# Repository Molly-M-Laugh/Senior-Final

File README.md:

## Welcome to Our Senior Design Project!

### Hardware

Put some base organization, hardware files in general should be put into the overall hardware folder unless:

- Microcontroller, should go into a designated section of software rather (TBD)
- Finalized circuits, hardware spec docs, and fabric designs (and others TBD) have specific hardware sub-folders

### Software

This folder includes our work on everything in our software stack. We have our code for our ESP32 handling BLE communication, IOS app code, our frontend website, and our backend api.

### Citations
We use a third party library that has been included into our repository because it was the only way to upload our work to the phone that we are developing on without deploying it. The library is called Alamofire, it's used for HTTP communication in Swift. You can find it at Software/BLE-IOS/Alamofire

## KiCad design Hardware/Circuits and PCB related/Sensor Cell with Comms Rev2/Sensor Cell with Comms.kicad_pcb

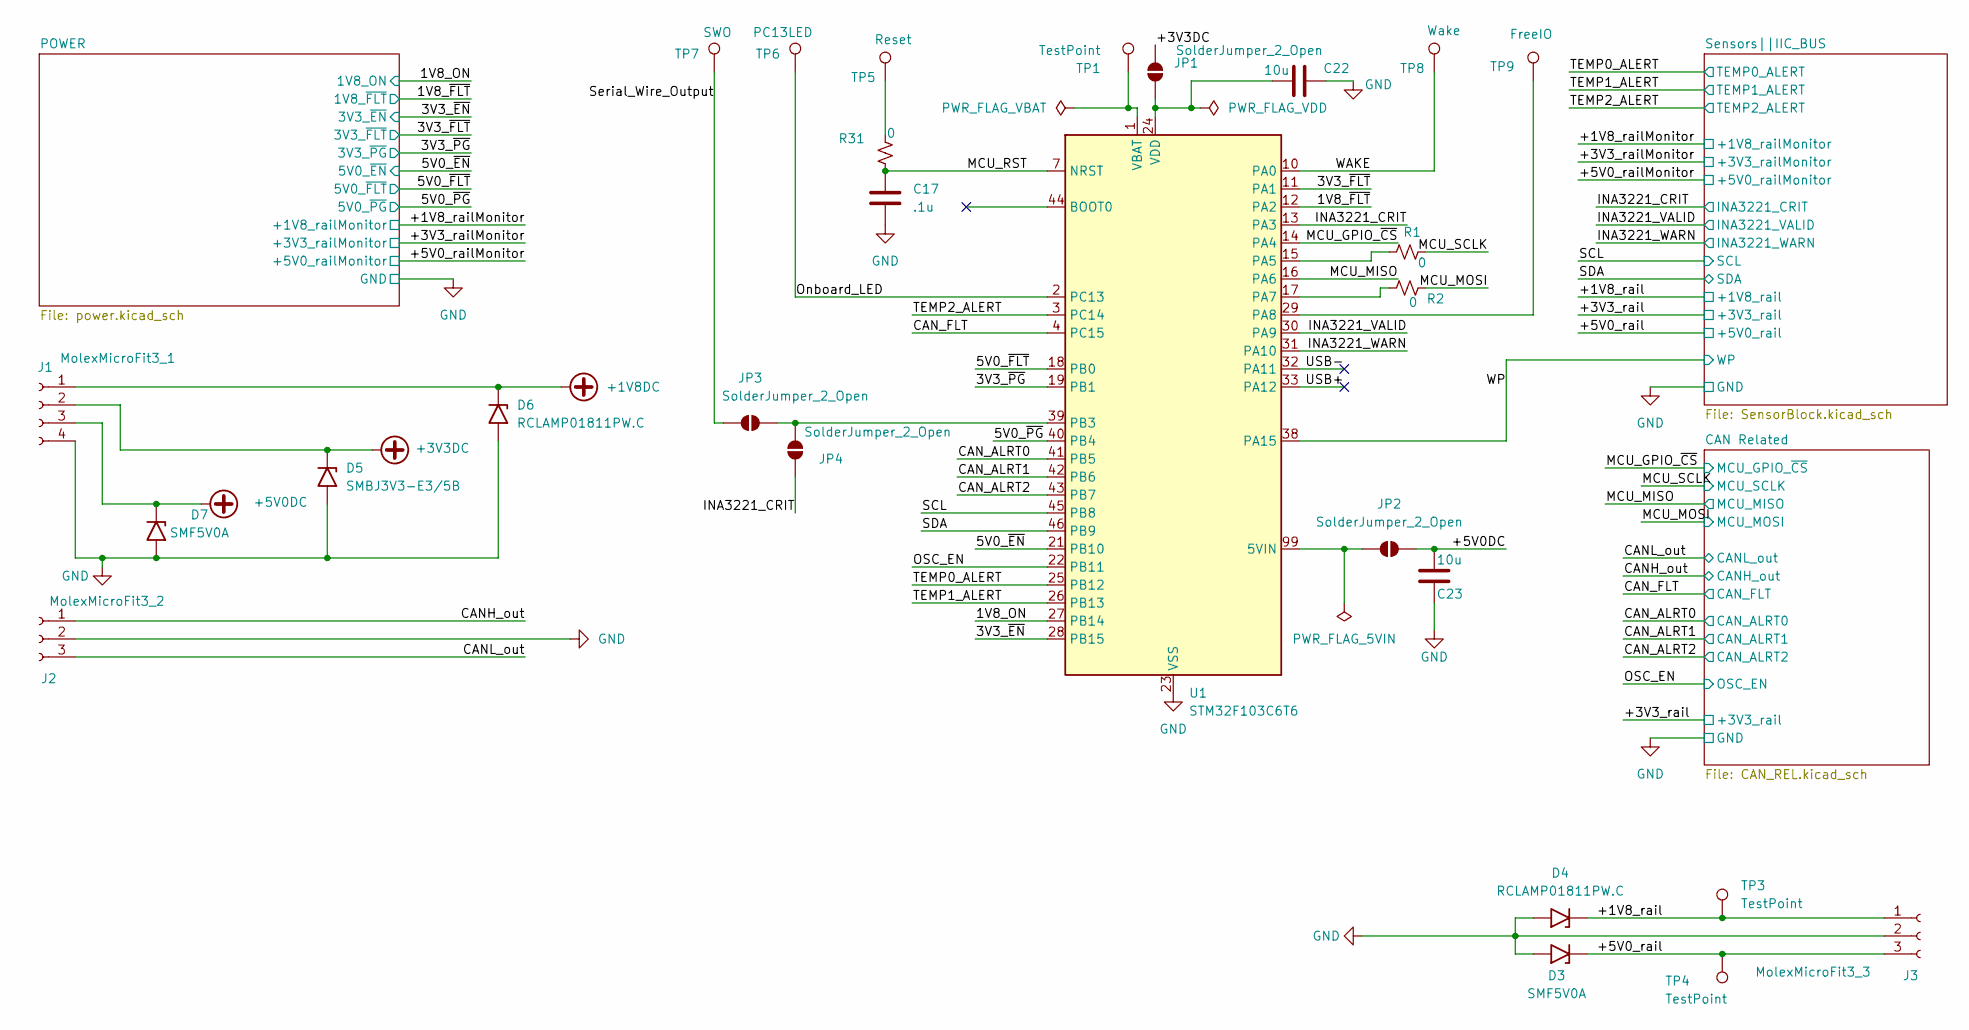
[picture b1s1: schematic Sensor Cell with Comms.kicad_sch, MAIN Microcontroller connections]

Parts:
C17: .1u; C_0805_2012Metric_Pad1.18x1.45mm_HandSolder
C22, C23: 10u; C_0603_1608Metric_Pad1.08x0.95mm_HandSolder
D3, D7: SMF5V0A; D_SMF
D4, D6: RCLAMP01811PW.C; D_SMF
D5: SMBJ3V3-E3/5B; D_SMF
J1: MolexMicroFit3_1; Molex_Micro-Fit_3.0_43650-0400_1x04_P3.00mm_Horizontal
J2: MolexMicroFit3_2; CONN_SD-43650-001_03_MOL
J3: MolexMicroFit3_3; CONN_SD-43650-001_03_MOL
JP1, JP2, JP3, JP4: SolderJumper_2_Open; SolderJumper-2_P1.3mm_Open_TrianglePad1.0x1.5mm
R1, R2, R31: 0; R_0603_1608Metric_Pad0.98x0.95mm_HandSolder
TP1, TP3, TP4: TestPoint; PinHeader_1x01_P1.00mm_Vertical
TP5: Reset; PinHeader_1x01_P1.00mm_Vertical
TP6: PC13LED; PinHeader_1x01_P1.00mm_Vertical
TP7: SWO; PinHeader_1x01_P1.00mm_Vertical
TP8: Wake; PinHeader_1x01_P1.00mm_Vertical
TP9: FreeIO; PinHeader_1x01_P1.00mm_Vertical
U1: STM32F103C6T6; PinHeader_1x20_P1.00mm_Verticalx2

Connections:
+1V8DC: D6.1 (A1), J1.1; also elsewhere on the board
+3V3DC: D5.1 (A1), J1.2, JP1.2 (B); also elsewhere on the board
+5V0DC: C23.2, D7.1 (A1), J1.3, JP2.2 (B); also elsewhere on the board
/1V8_ON: U1.27 (PB14); also elsewhere on the board
/1V8_~FLT: U1.12 (PA2); also elsewhere on the board
/3V3_~EN: U1.28 (PB15); also elsewhere on the board
/3V3_~FLT: U1.11 (PA1); also elsewhere on the board
/3V3_~PG: U1.19 (PB1); also elsewhere on the board
/5V0_~EN: U1.21 (PB10); also elsewhere on the board
/5V0_~FLT: U1.18 (PB0); also elsewhere on the board
/5V0_~PG: U1.40 (PB4); also elsewhere on the board
/+1V8_rail: D4.1 (A1), J3.1, TP3.1; also elsewhere on the board
/+5V0_rail: D3.1 (A1), J3.3, TP4.1; also elsewhere on the board
/CANH_out: J2.1; also elsewhere on the board
/CANL_out: J2.3; also elsewhere on the board
/CAN_ALRT0: U1.41 (PB5); also elsewhere on the board
/CAN_ALRT1: U1.42 (PB6); also elsewhere on the board
/CAN_ALRT2: U1.43 (PB7); also elsewhere on the board
/CAN_FLT: U1.4 (PC15); also elsewhere on the board
/INA3221_CRIT: JP4.2 (B), U1.13 (PA3); also elsewhere on the board
/INA3221_VALID: U1.30 (PA9); also elsewhere on the board
/INA3221_WARN: U1.31 (PA10); also elsewhere on the board
/MCU_GPIO_~CS: U1.14 (PA4); also elsewhere on the board
/MCU_MISO: U1.16 (PA6); also elsewhere on the board
/MCU_MOSI: R2.1; also elsewhere on the board
/MCU_RST: C17.1, R31.2, U1.7 (NRST)
/MCU_SCLK: R1.1; also elsewhere on the board
/OSC_EN: U1.22 (PB11); also elsewhere on the board
/Onboard_LED: TP6.1, U1.2 (PC13)
/SCL: U1.45 (PB8); also elsewhere on the board
/SDA: U1.46 (PB9); also elsewhere on the board
/Serial_Wire_Output: JP3.1 (A), TP7.1
/TEMP0_ALERT: U1.25 (PB12); also elsewhere on the board
/TEMP1_ALERT: U1.26 (PB13); also elsewhere on the board
/TEMP2_ALERT: U1.3 (PC14); also elsewhere on the board
/USB+: U1.33 (PA12)
/USB-: U1.32 (PA11)
/WAKE: TP8.1, U1.10 (PA0)
/WP: U1.38 (PA15); also elsewhere on the board
unnamed: JP2.1 (A), U1.99 (5VIN)
unnamed: JP3.2 (B), JP4.1 (A), U1.39 (PB3)
unnamed: R31.1, TP5.1
unnamed: R1.2, U1.15 (PA5)
unnamed: R2.2, U1.17 (PA7)
unnamed: TP9.1, U1.29 (PA8)
unnamed: TP1.1, U1.1 (VBAT)

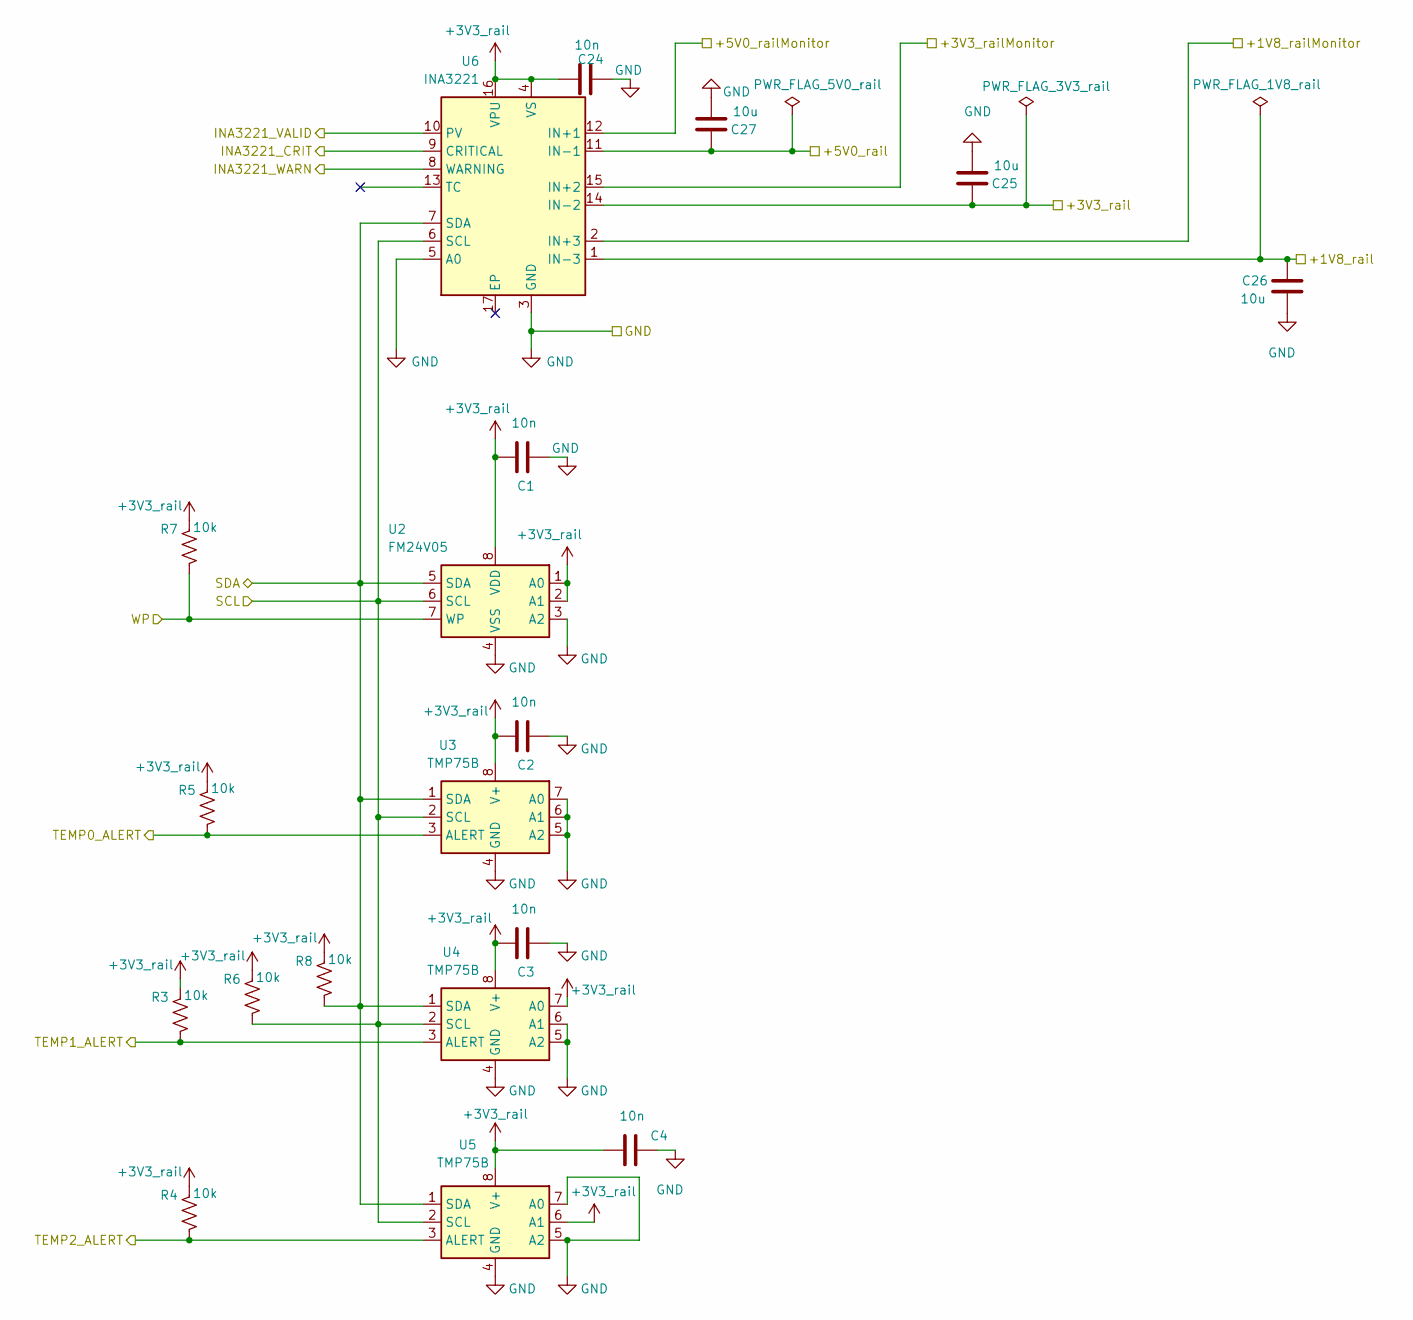
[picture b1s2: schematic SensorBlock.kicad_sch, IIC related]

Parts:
C1, C2, C3, C4, C24: 10n; C_0603_1608Metric_Pad1.08x0.95mm_HandSolder
C25, C26, C27: 10u; C_0603_1608Metric_Pad1.08x0.95mm_HandSolder
R3, R4, R5, R6, R7, R8: 10k; R_0603_1608Metric_Pad0.98x0.95mm_HandSolder
U2: FM24V05; SOIC-8_3.9x4.9mm_P1.27mm
U3, U4, U5: TMP75B; SO-8_3.9x4.9mm_P1.27mm
U6: INA3221; PinHeader_1x08_P1.00mm_Vertical_addedMonitorLines

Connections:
+3V3_rail: C1.2, C2.2, C3.2, C4.2, C24.2, C25.2, R3.2, R4.2, R5.2, R6.2, R7.2, R8.2, U2.1 (A0), U2.2 (A1), U2.8 (VDD), U3.8 (V+), U4.7 (A0), U4.8 (V+), U5.6 (A1), U5.8 (V+), U6.4 (VS), U6.14 (IN-2), U6.16 (VPU); also elsewhere on the board
/+1V8_rail: C26.2, U6.1 (IN-3); also elsewhere on the board
/+1V8_railMonitor: U6.2 (IN+3); also elsewhere on the board
/+3V3_railMonitor: U6.15 (IN+2); also elsewhere on the board
/+5V0_rail: C27.2, U6.11 (IN-1); also elsewhere on the board
/+5V0_railMonitor: U6.12 (IN+1); also elsewhere on the board
/INA3221_CRIT: U6.9 (CRITICAL); also elsewhere on the board
/INA3221_VALID: U6.10 (PV); also elsewhere on the board
/INA3221_WARN: U6.8 (WARNING); also elsewhere on the board
/SCL: R6.1, U2.6 (SCL), U3.2 (SCL), U4.2 (SCL), U5.2 (SCL), U6.6 (SCL); also elsewhere on the board
/SDA: R8.1, U2.5 (SDA), U3.1 (SDA), U4.1 (SDA), U5.1 (SDA), U6.7 (SDA); also elsewhere on the board
/TEMP0_ALERT: R5.1, U3.3 (ALERT); also elsewhere on the board
/TEMP1_ALERT: R3.1, U4.3 (ALERT); also elsewhere on the board
/TEMP2_ALERT: R4.1, U5.3 (ALERT); also elsewhere on the board
/WP: R7.1, U2.7 (WP); also elsewhere on the board

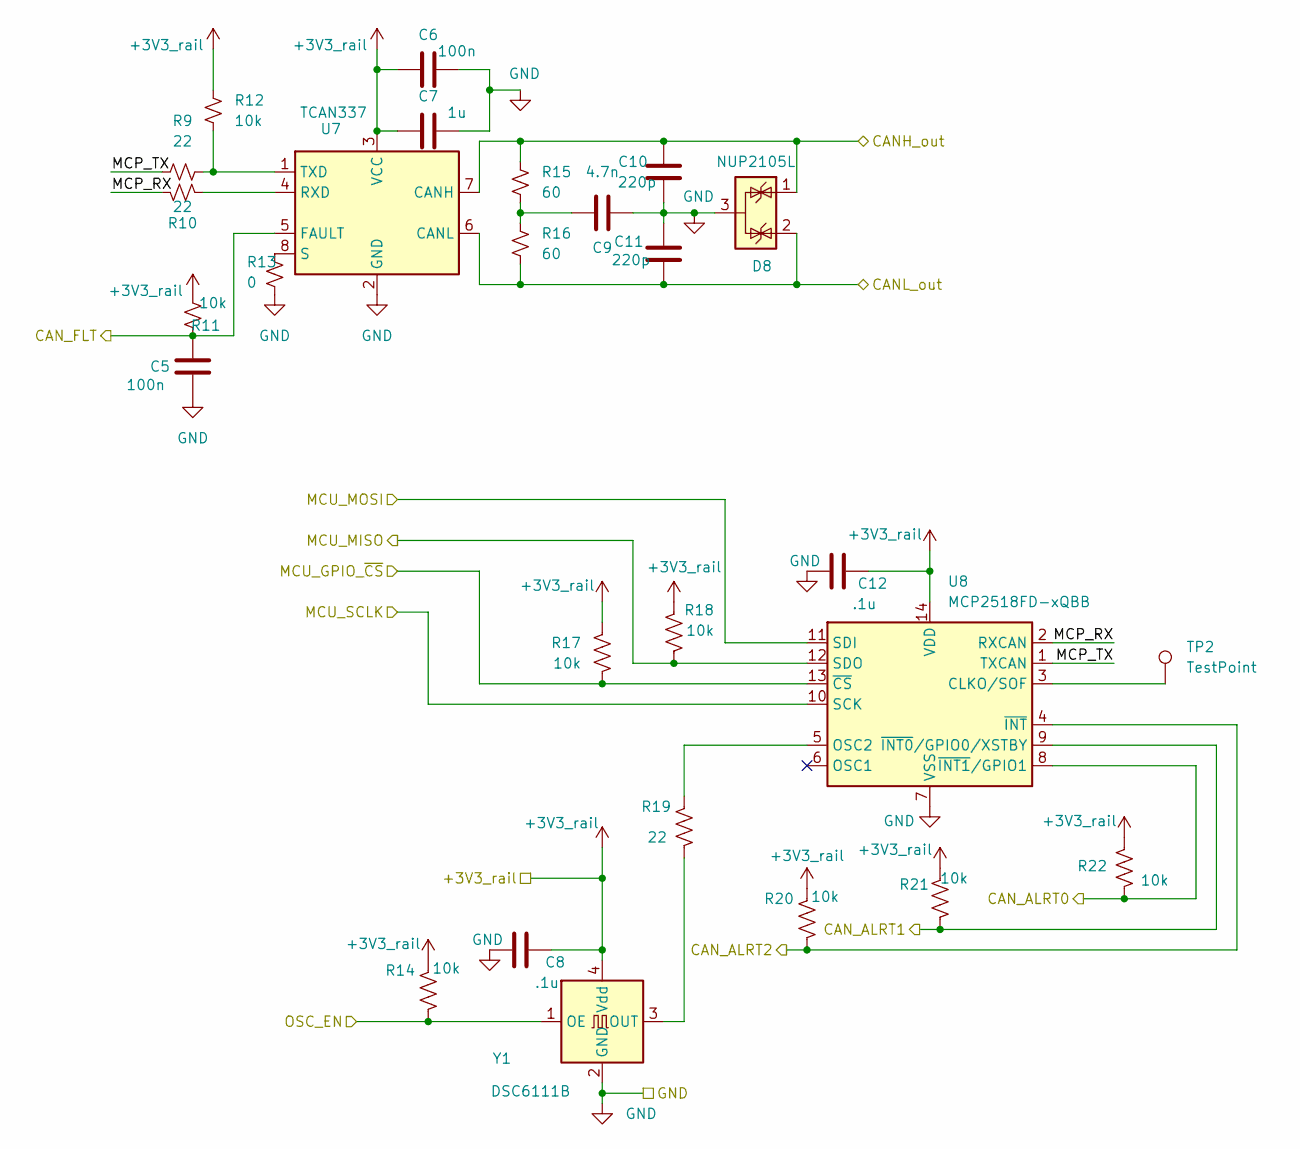
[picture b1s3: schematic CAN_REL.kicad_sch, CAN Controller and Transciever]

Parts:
C5, C6: 100n; C_0603_1608Metric_Pad1.08x0.95mm_HandSolder
C7: 1u; C_0603_1608Metric_Pad1.08x0.95mm_HandSolder
C8, C12: .1u; C_0603_1608Metric_Pad1.08x0.95mm_HandSolder
C9: 4.7n; C_0603_1608Metric_Pad1.08x0.95mm_HandSolder
C10, C11: 220p; C_0603_1608Metric_Pad1.08x0.95mm_HandSolder
D8: NUP2105L; SOT-23
R9, R10, R19: 22; R_0603_1608Metric_Pad0.98x0.95mm_HandSolder
R11, R12, R14, R17, R18, R20, R21, R22: 10k; R_0603_1608Metric_Pad0.98x0.95mm_HandSolder
R13: 0; R_0603_1608Metric_Pad0.98x0.95mm_HandSolder
R15, R16: 60; R_0603_1608Metric_Pad0.98x0.95mm_HandSolder
TP2: TestPoint; PinHeader_1x01_P1.00mm_Vertical
U7: TCAN337; SOIC-8_3.9x4.9mm_P1.27mm
U8: MCP2518FD-xQBB; SOIC-14_3.9x8.7mm_P1.27mm
Y1: DSC6111B; Oscillator_SMD_SiT_PQFN-4Pin_2.0x1.6mm

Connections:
+3V3_rail: C6.2, C7.2, C8.2, C12.2, R11.1, R12.2, R14.2, R17.2, R18.2, R20.2, R21.2, R22.2, U7.3 (VCC), U8.14 (VDD), Y1.4 (Vdd); also elsewhere on the board
/CAN Related/MCP_RX: R10.1, U8.2 (RXCAN)
/CAN Related/MCP_TX: R9.2, U8.1 (TXCAN)
/CANH_out: C10.2, D8.1 (K), R15.1, U7.7 (CANH); also elsewhere on the board
/CANL_out: C11.1, D8.2 (K), R16.2, U7.6 (CANL); also elsewhere on the board
/CAN_ALRT0: R22.1, U8.8 (~INT1/GPIO1); also elsewhere on the board
/CAN_ALRT1: R21.1, U8.9 (~INT0/GPIO0/XSTBY); also elsewhere on the board
/CAN_ALRT2: R20.1, U8.4 (~INT); also elsewhere on the board
/CAN_FLT: C5.2, R11.2, U7.5 (FAULT); also elsewhere on the board
/MCU_GPIO_~CS: R17.1, U8.13 (~CS); also elsewhere on the board
/MCU_MISO: R18.1, U8.12 (SDO); also elsewhere on the board
/MCU_MOSI: U8.11 (SDI); also elsewhere on the board
/MCU_SCLK: U8.10 (SCK); also elsewhere on the board
/OSC_EN: R14.1, Y1.1 (OE); also elsewhere on the board
unnamed: C9.1, R15.2, R16.1
unnamed: R10.2, U7.4 (RXD)
unnamed: R13.2, U7.8 (S)
unnamed: R9.1, R12.1, U7.1 (TXD)
unnamed: TP2.1, U8.3 (CLKO/SOF)
unnamed: R19.2, U8.5 (OSC2)
unnamed: R19.1, Y1.3 (OUT)

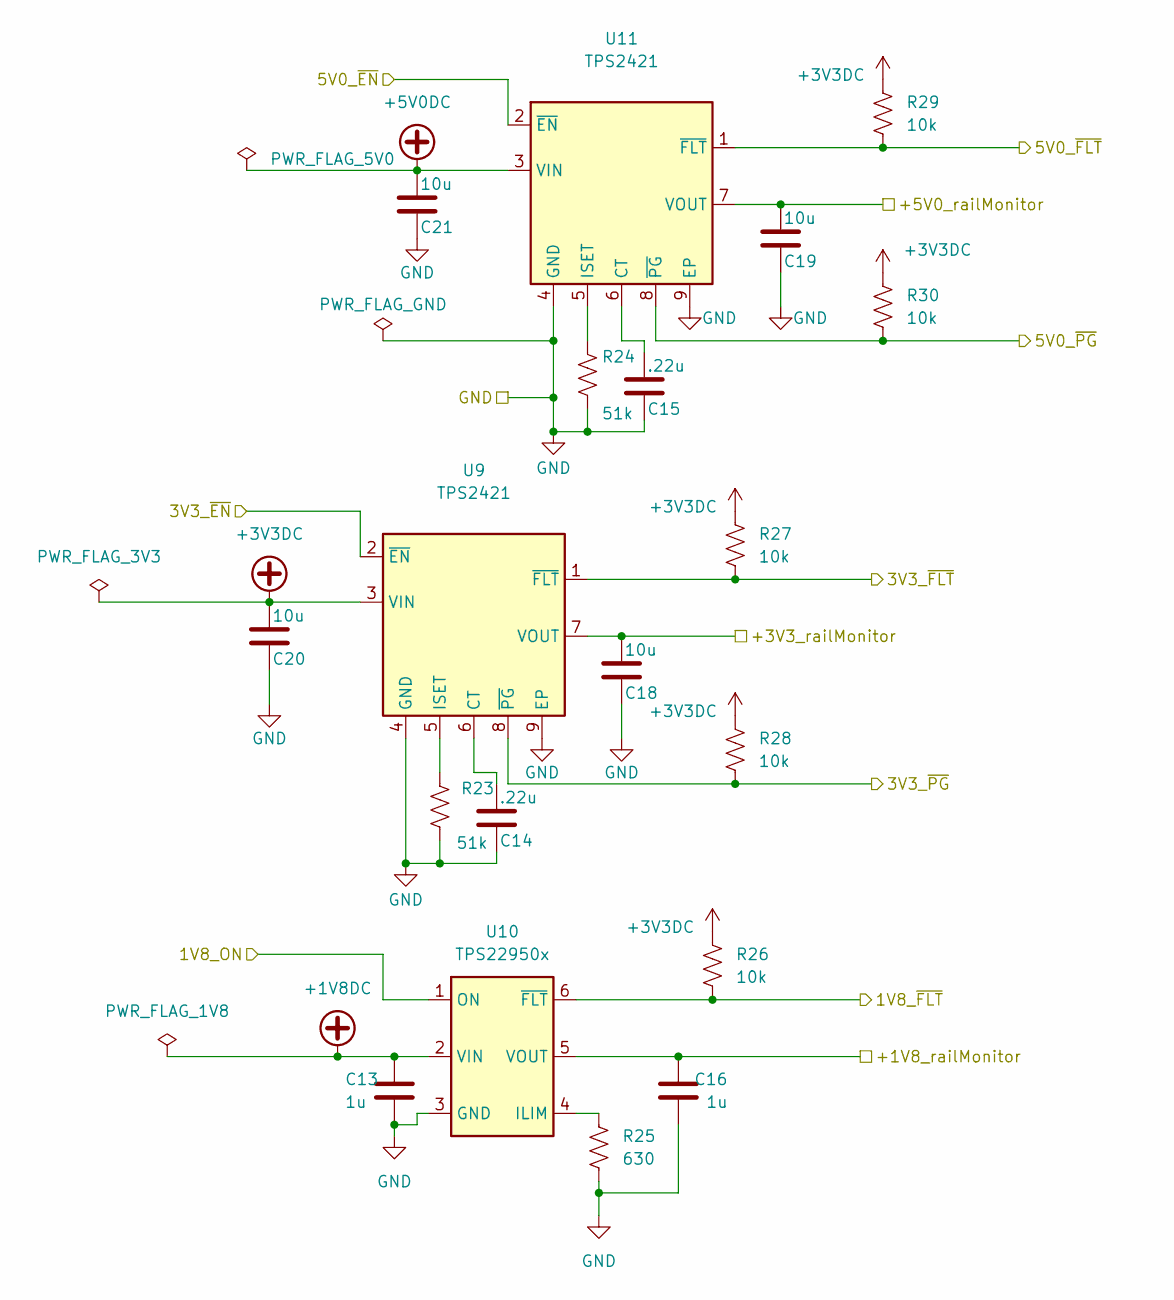
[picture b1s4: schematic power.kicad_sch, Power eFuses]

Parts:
C13, C16: 1u; C_0603_1608Metric_Pad1.08x0.95mm_HandSolder
C14, C15: .22u; C_0603_1608Metric_Pad1.08x0.95mm_HandSolder
C18, C19, C20, C21: 10u; C_0603_1608Metric_Pad1.08x0.95mm_HandSolder
R23, R24: 51k; R_0603_1608Metric_Pad0.98x0.95mm_HandSolder
R25: 630; R_0603_1608Metric_Pad0.98x0.95mm_HandSolder
R26, R27, R28, R29, R30: 10k; R_0603_1608Metric_Pad0.98x0.95mm_HandSolder
U9, U11: TPS2421; HSOP-8-1EP_3.9x4.9mm_P1.27mm_EP2.41x3.1mm_ThermalVias
U10: TPS22950x; SOT-23-6

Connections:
+1V8DC: C13.2, U10.2 (VIN); also elsewhere on the board
+3V3DC: C20.2, R26.2, R27.2, R28.2, R29.2, R30.2, U9.3 (VIN); also elsewhere on the board
+5V0DC: C21.2, U11.3 (VIN); also elsewhere on the board
/1V8_ON: U10.1 (ON); also elsewhere on the board
/1V8_~FLT: R26.1, U10.6 (~FLT); also elsewhere on the board
/3V3_~EN: U9.2 (~EN); also elsewhere on the board
/3V3_~FLT: R27.1, U9.1 (~FLT); also elsewhere on the board
/3V3_~PG: R28.1, U9.8 (~PG); also elsewhere on the board
/5V0_~EN: U11.2 (~EN); also elsewhere on the board
/5V0_~FLT: R29.1, U11.1 (~FLT); also elsewhere on the board
/5V0_~PG: R30.1, U11.8 (~PG); also elsewhere on the board
/+1V8_railMonitor: C16.2, U10.5 (VOUT); also elsewhere on the board
/+3V3_railMonitor: C18.2, U9.7 (VOUT); also elsewhere on the board
/+5V0_railMonitor: C19.2, U11.7 (VOUT); also elsewhere on the board
unnamed: C14.2, U9.6 (CT)
unnamed: R23.2, U9.5 (ISET)
unnamed: R25.2, U10.4 (ILIM)
unnamed: C15.2, U11.6 (CT)
unnamed: R24.2, U11.5 (ISET)

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
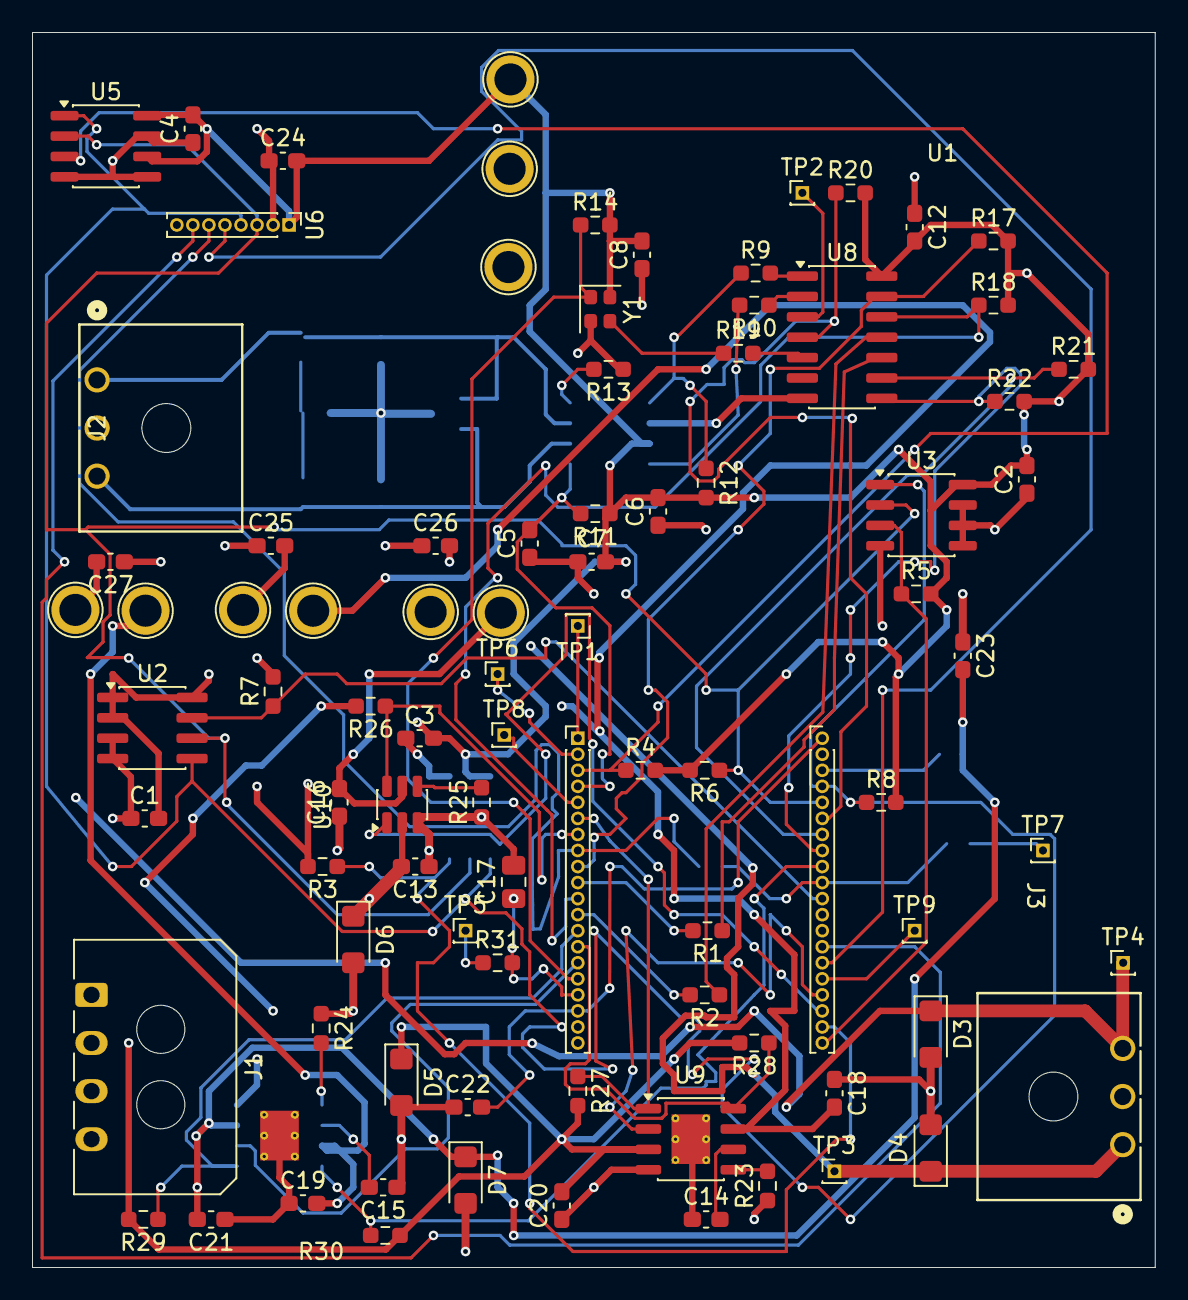
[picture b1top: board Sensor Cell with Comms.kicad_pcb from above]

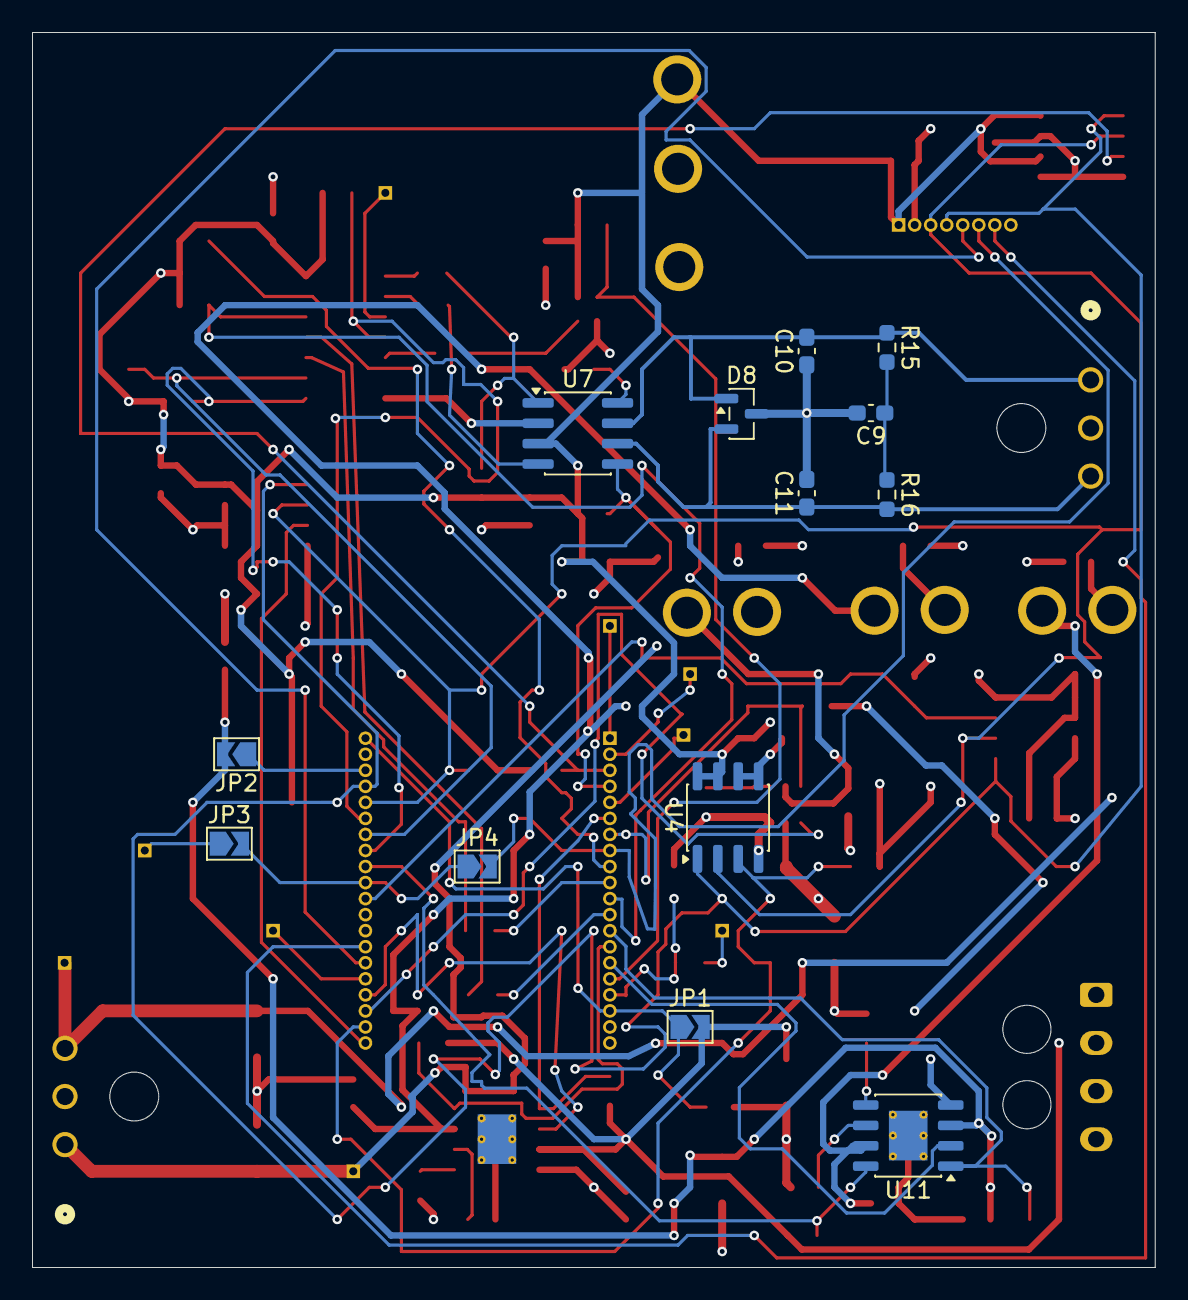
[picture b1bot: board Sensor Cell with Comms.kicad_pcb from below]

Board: 4 copper layers, 70.0 x 77.0 mm, 92 parts (13 on the bottom side), 64 nets.

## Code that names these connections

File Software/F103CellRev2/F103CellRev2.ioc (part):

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Mcu.Name=STM32F103C(4-6)Tx
Mcu.Package=LQFP48
Mcu.UserName=STM32F103C6Tx
PA0-WKUP.GPIOParameters=GPIO_Label
PA0-WKUP.GPIO_Label=WAKE
PA0-WKUP.Mode=SYS_WakeUp0
PA0-WKUP.Signal=SYS_WKUP
PA1.GPIOParameters=GPIO_Label,GPIO_ModeDefaultEXTI
PA1.GPIO_Label=FLT_3V3
PA1.GPIO_ModeDefaultEXTI=GPIO_MODE_IT_FALLING
PA1.Signal=GPXTI1
PA10.GPIOParameters=GPIO_Label,GPIO_ModeDefaultEXTI
PA10.GPIO_Label=INA3221_WARN
PA10.GPIO_ModeDefaultEXTI=GPIO_MODE_IT_FALLING
PA10.Signal=GPXTI10
PA11.GPIOParameters=GPIO_Label
PA11.GPIO_Label=USB-
PA11.Mode=Device
PA11.Signal=USB_DM
PA12.GPIOParameters=GPIO_Label
PA12.GPIO_Label=USB+
PA12.Mode=Device
PA12.Signal=USB_DP
PA13.Mode=Serial_Wire
PA13.Signal=SYS_JTMS-SWDIO
PA14.Mode=Serial_Wire
PA14.Signal=SYS_JTCK-SWCLK
PA15.GPIOParameters=PinState,GPIO_Label
PA15.GPIO_Label=WP
PA15.PinState=GPIO_PIN_SET
PA15.Signal=GPIO_Output
PA2.GPIOParameters=GPIO_Label,GPIO_ModeDefaultEXTI
PA2.GPIO_Label=FLT_1V8
PA2.GPIO_ModeDefaultEXTI=GPIO_MODE_IT_FALLING
PA2.Signal=GPXTI2
PA3.GPIOParameters=GPIO_Label,GPIO_ModeDefaultEXTI
PA3.GPIO_Label=INA3221_CRIT
PA3.GPIO_ModeDefaultEXTI=GPIO_MODE_IT_FALLING
PA3.Signal=GPXTI3
PA4.GPIOParameters=PinState,GPIO_Label
PA4.GPIO_Label=SPI_CS
PA4.PinState=GPIO_PIN_SET
PA4.Signal=GPIO_Output
PA5.GPIOParameters=GPIO_Label
PA5.GPIO_Label=MCU_SCLK
PA5.Mode=Full_Duplex_Master
PA5.Signal=SPI1_SCK
PA6.GPIOParameters=GPIO_Label
PA6.GPIO_Label=MCU_MISO
PA6.Mode=Full_Duplex_Master
PA6.Signal=SPI1_MISO
PA7.GPIOParameters=GPIO_Label
PA7.GPIO_Label=MCU_MOSI
PA7.Mode=Full_Duplex_Master
PA7.Signal=SPI1_MOSI
PA8.GPIOParameters=GPIO_Label
PA8.GPIO_Label=FreeIO
PA8.Signal=GPIO_Output
PA9.GPIOParameters=GPIO_Label,GPIO_ModeDefaultEXTI
PA9.GPIO_Label=INA3221_VALID
PA9.GPIO_ModeDefaultEXTI=GPIO_MODE_IT_FALLING
PA9.Signal=GPXTI9
PB0.GPIOParameters=GPIO_Label,GPIO_ModeDefaultEXTI
PB0.GPIO_Label=FLT_5V0
PB0.GPIO_ModeDefaultEXTI=GPIO_MODE_IT_FALLING
PB0.Signal=GPXTI0
PB1.GPIOParameters=GPIO_Label
PB1.GPIO_Label=PG3V3
PB1.Signal=GPIO_Input
PB10.GPIOParameters=PinState,GPIO_Label
PB10.GPIO_Label=EN5V0
PB10.PinState=GPIO_PIN_SET
PB10.Signal=GPIO_Output
PB11.GPIOParameters=GPIO_Label
PB11.GPIO_Label=OSC_EN
PB11.Signal=GPIO_Output
PB12.GPIOParameters=GPIO_Label,GPIO_ModeDefaultEXTI
PB12.GPIO_Label=TEMP0_ALERT
PB12.GPIO_ModeDefaultEXTI=GPIO_MODE_IT_FALLING
PB12.Signal=GPXTI12
PB13.GPIOParameters=GPIO_Label,GPIO_ModeDefaultEXTI
PB13.GPIO_Label=TEMP1_ALERT
PB13.GPIO_ModeDefaultEXTI=GPIO_MODE_IT_FALLING
PB13.Signal=GPXTI13
PB14.GPIOParameters=GPIO_Label
PB14.GPIO_Label=ON1V8
PB14.Signal=GPIO_Output
PB15.GPIOParameters=PinState,GPIO_Label
PB15.GPIO_Label=EN3V3
PB15.PinState=GPIO_PIN_SET
PB15.Signal=GPIO_Output
PB3.GPIOParameters=GPIO_Label
PB3.GPIO_Label=SingleWireOutput
PB3.Signal=SYS_JTDO-TRACESWO
PB4.GPIOParameters=GPIO_Label,GPIO_ModeDefaultEXTI
PB4.GPIO_Label=PG5V0
PB4.GPIO_ModeDefaultEXTI=GPIO_MODE_IT_FALLING
PB4.Signal=GPXTI4
PB5.GPIOParameters=GPIO_Label,GPIO_ModeDefaultEXTI
PB5.GPIO_Label=CAN_ALRT0
PB5.GPIO_ModeDefaultEXTI=GPIO_MODE_IT_FALLING
PB5.Signal=GPXTI5
PB6.GPIOParameters=GPIO_Label,GPIO_ModeDefaultEXTI
PB6.GPIO_Label=CAN_ALRT1
PB6.GPIO_ModeDefaultEXTI=GPIO_MODE_IT_FALLING
PB6.Signal=GPXTI6
PB7.GPIOParameters=GPIO_Label,GPIO_ModeDefaultEXTI
PB7.GPIO_Label=CAN_ALRT2
PB7.GPIO_ModeDefaultEXTI=GPIO_MODE_IT_FALLING
PB7.Signal=GPXTI7
PB8.GPIOParameters=GPIO_Label
PB8.GPIO_Label=SCL
PB8.Mode=I2C
PB8.Signal=I2C1_SCL
PB9.GPIOParameters=GPIO_Label
PB9.GPIO_Label=SDA
PB9.Mode=I2C
PB9.Signal=I2C1_SDA
PC13-TAMPER-RTC.GPIOParameters=GPIO_Label
PC13-TAMPER-RTC.GPIO_Label=OnboardLED
PC13-TAMPER-RTC.Signal=GPIO_Output
PC14-OSC32_IN.GPIOParameters=GPIO_Label,GPIO_ModeDefaultEXTI
PC14-OSC32_IN.GPIO_Label=TEMP2_ALERT
PC14-OSC32_IN.GPIO_ModeDefaultEXTI=GPIO_MODE_IT_FALLING
PC14-OSC32_IN.Signal=GPXTI14
PC15-OSC32_OUT.GPIOParameters=GPIO_Label,GPIO_ModeDefaultEXTI
PC15-OSC32_OUT.GPIO_Label=CAN_FLT
PC15-OSC32_OUT.GPIO_ModeDefaultEXTI=GPIO_MODE_IT_FALLING
PC15-OSC32_OUT.Signal=GPXTI15
PD0-OSC_IN.Mode=HSE-External-Oscillator
PD0-OSC_IN.Signal=RCC_OSC_IN
PD1-OSC_OUT.Mode=HSE-External-Oscillator
PD1-OSC_OUT.Signal=RCC_OSC_OUT
RCC.SYSCLKFreq_VALUE=72000000
RCC.SYSCLKSource=RCC_SYSCLKSOURCE_PLLCLK
board=custom

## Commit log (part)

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2026-01-02 Adding base design folders
    Please remove the keep.txt once files are added to that folder, is just so GitHub would see the file for upload.
2026-01-02 Create README.md
    Describing current drafted layout
2026-01-02 Added safety docs
    IEC documents on safety, hazards, batteries, etc
2026-01-10 Removed the added RouterLink while is only one page
2026-01-10 Readded RouterLink as routing still not retrieved, added zone.js for local routing
2026-01-10 Forgot to ng build, now seeing if changes cascade to heroku
2026-01-10 Trying some build path changes
2026-01-10 Continuing to find alternative routing for newer node version
2026-01-10 Rolling back package.json and server.js changes
2026-01-10 Forgot to rename server paths from lab3
2026-01-11 Forgot ng build, redoing to see Heroku changes
2026-01-11 Added zone.js to component's .ts files to see effect
2026-01-11 Attempting to find heroku routing again
2026-01-11 Cloned lab 3 on last working heroku branch, now working on confirming heroku acceptance
2026-01-11 Forgot to resolve one merge conflicted file
2026-01-11 Removed and/or renamed components and references to reflect senior project's pages
2026-01-18 Added fabric docs
2026-01-19 Testing login without form live updates/routing with auth included
2026-01-19 Added empty function to check login display currently
2026-01-19 Forgot name of form group
2026-01-19 Now can see password input box, added but not linking auth/mailer under services folder
2026-01-29 Switched to earlier version to work on pure routing before try authentication
2026-02-01 Added sewing/surger documentation
    For future work or report reference
2026-02-02 Confirmed high chance is an ssr issue for any auto routes to an ngform, will work on ssr now
2026-02-03 Added SSR so that base page can point to a form without invalidating the form
2026-02-03 Forgot npm install, and changed output directory to reflect newer angular ssr
2026-02-07 Adding last of base pages for routing before additional authentication, sql access
2026-02-07 Adding BLE communication work from past month
2026-02-10 Rename Cell Supervisor.pdf to Cell Supervisor. rev1pdf
2026-02-10 Rename Cell Supervisor. rev1pdf to Cell Supervisor_rev1.pdf
2026-02-14 Added some base components for local sql server connection, but need to set up HTTPClient
2026-02-14 Added HTTPClient, now debugging connection to local server
2026-02-14 Added components for initial connection from nodejs to postgres, but have to fix issue with angular/nodejs firewall
2026-02-17 Added comments, removed code for testing BLE functionality.
2026-02-17 Made progress in trying to implement the browser side rendering graph library, but will shift real quick to finding/using an SSR safe graph library
2026-02-18 Added Heroku allowed origins
2026-02-18 Heroku having a general issue saying cors not defined, so with no SQL currently dropping cors origin verification for now
2026-02-21 Create info.txt
    info about items in this folder and subfolders
2026-02-22 Making work on getting cors working, as is inter-server connection issue based on Dev Tools
2026-02-22 Wanted to complete local SQL and knew where base issues were, so got feedback on CORS/API location, URL slight syntax and visability, and additional routing/button hold on registration
2026-02-22 Changing heroku postbuild to see both angular and nodejs?
2026-02-22 Changing heroku postbuild to see both angular and nodejs v2?
2026-02-22 Changing heroku postbuild to see both angular and nodejs v3?
2026-02-22 Trying fix 1 to get working with client
2026-02-22 For TypeError: Cannot destructure property 'username' of 'req.body' as it is undefined, removed return part of statement
2026-02-22 Added result back in now that added json parsing for client
2026-02-22 Added extension to heroku side, and added await for query response
2026-02-22 Adding all IOS work, and modified the ESP file to match the IOS code
2026-02-24 Create battery_pms_charger
2026-02-24 Got a different option from CanvasJS working. This is the baseline of it, will edit more later.
2026-02-27 Driver imported, along with headers for I/O
2026-02-28 Added SQL queries to login, as well as added graphing package
2026-03-01 Add KiCad hardware project; normalize LF; ignore lock files
2026-03-02 KiCad hardware files
2026-03-02 TCAN337 Wiring diagram redone to include the componenent sizing for the pcb stage
2026-03-02 need to finish TPS22950x model and wiring but good now for the rest. After wiring diag is done finish actual wiring and move onto PCB process
2026-03-03 TPS22950x model done and included
2026-03-03 hardware re-work mostly done, need to finish EXTq mapping. So far INTs are grouped into 4 banks, PB2,3,4 are reserved, so map those to something else if needed. CAN FLTS is on bank3, Power FLTS is ba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
2026-03-04 mostly done with schematic, need to add FRAM chip, ESP<-->STM, and finish the MCP2518 crystal selection and supporting caps for crystal, wants 40 MHz
2026-03-04 added files for the oscillator for the MCP, finished wiring connections in general, need to finish the footprint for the osc and then make PCB using the provided autogenerated nets from KICAD
2026-03-07 Footprint for Osc done, osc wired to MCP and STM wired to Osc. I need to make the pcb now, and then determine what type of connector to use. Things to keep in mind when choosing; Needs to either supp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
2026-03-07 forgot pdf of schematic
2026-03-17 Added updated version that tested and lasted
    Connection with Windows 11 is stable with addition of its specific services
2026-03-17 Added breakout header pins to footprints for STM and MCP2518, need to make MCU master table, EXTI# summary table, and device connection table
2026-03-17 Finished schematic, added all footprints, finishing ERC now to move onto the PCB planner to have Kicad do most of the heavy lifting
2026-03-19 Schematic done, and ERC passes successfully. Move onto PCB now that this is completed
2026-03-19 (wip) BLE angular progression for now trying to do over angular/browser rather than node with additional hardware access nedded
2026-03-20 Updated for actual connection functionality
    To connect to the ESP32 over browser, needed to add two descriptors in order for mutual recognition
2026-03-20 Locally have a near perfect synch for BLE. Testing on Heroku before moving to database storage
2026-03-20 Readjusted variables for Heroku deployment
2026-03-20 Adding Date Time Functionality to graph
2026-03-20 Added logic for graphs, cleaned up some code before adding to data storage
2026-03-21 PCB finished, need final approval from Maxted, changed connector to Molex minifit3
2026-03-21 Demo circuit for CAN functionality
2026-03-24 Made changes for local, now trying Heroku, for uploading data live from ESP32 to database
2026-03-24 Making one change to maybe fix data issue on Heroku by moving connect placement
2026-03-24 Adding HTTP requests and responses for login and register. Adding 3rd party library Alamofire to the app.
2026-03-28 minor change to UI, and change from last commit to userinterfacestate
2026-03-28 adding test for status code feedback in auth
2026-03-28 reverting change
2026-03-28 retrying change to status code
2026-03-28 testing communications, adding bug for testing
2026-03-28 testing different method for status code
2026-03-28 fixing bug on front end from error codes
2026-03-30 potential bug fix for web login with status code errors
2026-04-05 testing tokens v1
2026-04-05 Updated local BLE to include interface for parsing BLE, typescript updates, Heroku client update, and new graph logic
2026-04-08 Found a GUI driven code tool, lets me configure every pin via a GUI and now we just need to write the logical steps of what signals do what. Need to Re-add the MCP2518 open source driver since I dele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
2026-04-09 Trying bug fix for auth
2026-04-09 Bug fix attempt 3
2026-04-09 Testing to ensure auth functionality
2026-04-09 auth is broken, testing another fix
2026-04-09 Fixed auth, reattempting cookies
2026-04-11 STM32 core firmware complete - builds clean (0 errors, 0 warnings)
    Flash usage: 31KB/32KB at -O0. Switch to -Os for release to recover headroom.
    TODO:
    - Bench: run I2C scan to confirm TMP75B U4/U5 addresses (placeholders 0x49, 0x4B)
    - Bench: update shunt resistor values in ina3221_port.h
    - Define CAN message ID scheme and tighten RX filter
    - Implement TPS2421 latch-off recovery policy
2026-04-12 Got axis fixed, started shift in color scheme/design from website front page
2026-04-13 Adding inital Menu functionality, rearranging UI structure
2026-04-14 Forgot to commit Heroku oriented changes before pushing to Heroku
2026-04-14 Working on fixing client
2026-04-14 Working on fixing clientv2
2026-04-18 Got ESP interface done, colin and molly go thru and rip apart as necessary
2026-04-19 Small functional fix to the menu, needs to change later
2026-04-19 Testing client on Heroku
2026-04-19 Testing client on Heroku, via pool changes
2026-04-19 Checking data-init
2026-04-19 Checking initial load data points
2026-04-19 Confirmed empty retrieval, working on finding where filter empties
2026-04-19 Checking for any non empty response
2026-04-19 Reworked filter still empties, continuing to tune
2026-04-19 Due to Heroku type possible mismatch, trying regex
2026-04-19 May have forgotten to implement syntax issue fix to Heroku version of data queries
2026-04-19 Dependencies for Colin to build
2026-04-22 Had to move all files to new project setup due to misconfig, Add application layer modules: power_ctrl, fault_ctrl, fram_port, ina3221_port, tmp75b_port, can_ctrl, mcp_port, telemetry, self_test, app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
2026-04-23 BLE ESP32 skeleton, will later modify to match I2C messages. copied windows compatibility changes into BLECommunication.ino
2026-04-28 Starting UI rework, via the login first
2026-04-28 Login and new user updates
2026-04-28 Removed extra elements from login
2026-04-28 Reverted login to original, added design for home page
2026-04-29 Finished sim layer for collin. Made edits to BLEconnect.swift to correctly parse incoming frames from CAN. xCode compile is saying Could not cast value of type '__NSCFNumber' to 'NSString', could be 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
2026-04-29 Changes to UI, better handling of login, overhaul of app navigation, added sidebar menu
2026-04-30 BLE mimic finished, enjoy
2026-05-01 Attempt at implementing HID mask for BLE communication
2026-05-02 Cleaned up server.js, removed all or near all old name references
2026-05-02 Renaming of tab to project name
2026-05-02 Changed filtering for ESP connection
2026-05-02 Confirming initial changes to ble for website for data
2026-05-02 Added new uuid of data characteristic
2026-05-02 changes to how graph works internally
2026-05-02 Removed BLE from nodejs as handled on Angular
2026-05-03 Changed name of ESP, small fixes to BLE
2026-05-03 Trying utf-16
2026-05-03 Trying utf-16le
2026-05-03 Trying utf-16be
2026-05-03 Added timer delay for BLE notify messages
2026-05-03 Specifying interface to help
2026-05-03 Checking interface isn't reading nothing or is reading the sine wave
2026-05-03 Checking interface with delay to allow sine wave change
2026-05-04 Checking interface with delay to allow sine wave changeV3
2026-05-04 Checking interface with delay to allow sine wave changeV4
2026-05-04 Checking interface with delay to allow sine wave changeV5
2026-05-04 Checking interface with delay to allow sine wave changeV7
2026-05-04 Checking interface with delay to allow sine wave changeV8
2026-05-04 Changing Database to work with four temperature columns
2026-05-04 Changing Database to work with four temperature columnsV2
2026-05-04 Changing Database to work with four temperature columnsV3
2026-05-04 Changing Database to work with four temperature column V5, debugging SQL
2026-05-04 Changing Database to work with four temperature column V6, wrong decimal amount testing
2026-05-04 Changing Database to work with four temperature column V8, confirming proper response back
2026-05-04 Confirmed data returns back properly, adding y-axis label
2026-05-04 Y-label threshold line was for F, not C
2026-05-05 Rename Sensor Cell with Comms-Sensors--IIC_BUS.svg to Sensor Cell with Comms-Sensors--IIC_BUS.svg
    Replaced || with -- for Windows pull ability
2026-05-05 Rename Sensor Cell with Comms-Sensors||IIC_BUS.svg to Sensor Cell with Comms-Sensors--IIC_BUS.svg
    Replacement of || with -- for windows ability to pull.
